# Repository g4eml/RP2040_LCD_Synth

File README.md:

# RP2040_LCD_Synth

## Description

This Project is a development of the RP2040_Synth project with the addition of a Touch screen LCD display module, refered to here as the HMI Module (Human Machine Interface). This is intended to be used as a piece of test equipment. 
Currently supports 4 different type of synthesiser chip, the ADF4351, the Max2870, the LMX2595 and the ADF5355.

## Features

Control and configuration can be done from the Touch Screen or from a USB serial port connection. 

No special programming hardware or software required. 

Serial programming using the RP2040s built in USB serial port and standard boot loader. 

Settings are saved to EEPROM for automatic load on power on.

Support for FSK CW Identification for beacon use.

Supports data modes for Beacon Identification.  JT4G is available on all chip types. Q65 is only available on the LMX2595 and ADF5355.

Note:- Whilst JT4G mode is available on all chips there may be some limitations. The ADF4351 and MAX2870 chips have a limited frequency resolution and may not be able to accurately set the required tone frequencies especially when an external multiplication chain is used.

Supports GPS connection for the accurate timing required for data modes. 

Supports 10 different channels which can also be selected by external switches. 

Supports External Key Input with independently configurable FSK Shift. 

Default register settings can be loaded for all synthesiser types to produce some initial RF output. This is often the hardest thing to do with a new chip type.

Supports use with an external frequency multiplier for the higher microwave bands. Allows frequency entry and display of the final output frequency. Adjusts FSK shifts to compensate for multiplication factor.  

Direct output frequency and phase detector frequency entry. Register values are calculated automatically.  

## Requirements

This code was designed to work with the Elecrow CrowPanel Pico-3.5 inch 480x320 TFT LCD HMI Module. https://www.aliexpress.com/item/1005007250778536.html 

Note:- similar HMI Panels are available using the ESP32 processor chip. Make sure that you are purchasing the RP2040 version. 

## Alternative Display

The correct module now appears to be difficult to obtain. A new interface board has been designed to allow a Raspberry Pi Pico to be fitted to a more easily available 3.5" TFT touch panel. Full Details can be found in the PCB folder. 

The LCD screen, controller chip and Touch Screen controller appear to be exactly the same as the original module.
 
If you are searching for these online the critical points are that it needs to be a 3.5" display  320 x 480 resolution with an ILI9488 controller and touch screen. 
There are lots of similar displays out there but the correct ones are usually Red and have 14 connections at one end of the board and 4 connections at the other. Be careful as these are also available without the touch screen. 
Full schematic and PCB designs are in the PCB folder. 

## Synthesisers

Suitable Synthesiser boards are available from Ebay, Amazon, Ali Express, SV1AFN etc. 

If you wish to use the data modes you will also need a GPS module to provide the necessary accurate timing.  

## Connecting

All of the various synthesiser moduels use different connectors and pinouts.

The simplest solution is to make an adaptor cable that plugs into the GP connector of the HMI module and fit suitable plugs for the modules to the other end. Keep the wiring as short as possible. Probably no more than 100mm long. 

The power can be provided by the USB-C connector marked 'USB' on the end of the HMI module

## Programming or updating the HMI Module (quick method)

This can be done either before or after the Syntesiser has been connected, it makes no difference. Updating to a new firmware version is done the same way.   

1. Locate the latest compiled firmware file 'RP2040_LCD_Synth.uf2' which will be found here https://github.com/g4eml/RP2040_LCD_Synth/releases and save it to your desktop. 

2. Connect the HMI Module to your PC using the USB-C port on the side. 

3. Hold down the BOOT button on the back of the HMI module and briefly press the Reset button. The RP2040 should appear as a USB disk drive on your PC.

3. Copy the .uf2 file onto the USB drive. The RP2040 will recognise the file and immediately update its firmware and reboot.

## Building your own version of the firmware (longer method and not normally required)

The RP2040 is programmed using the Arduino IDE with the Earl F. Philhower, III  RP2040 core. 

#### Installing the Arduino IDE

1. Download and Install the Arduino IDE 2.3.0 from here https://www.arduino.cc/en/software

2. Open the Arduino IDE and go to File/Preferences.

3. in the dialog enter the following URL in the 'Additional Boards Manager URLs' field: https://github.com/earlephilhower/arduino-pico/releases/download/global/package_rp2040_index.json

4. Hit OK to close the Dialog.

5. Go to Tools->Board->Board Manager in the IDE.

6. Type “RP2040” in the search box.

7. Locate the entry for 'Raspberry Pi Pico/RP2040 by Earle F. Philhower, III' and click 'Install'

### Installing the required libraries

1. From the Arduino IDE select (Tools > Manage Libraries)
2. Search for 'JTEncode' Scroll down to find the Etherkit JTEncode library by Jason Milldrum.
3. Click Install
4. Now search for 'TFT_eSPI' and find the TFT graphics library by Bodmer.
5. Click Install

#### Downloading the Software.

1. Download the latest released source code .zip file from https://github.com/g4eml/RP2040_LCD_Synth/releases

2. Save it to a convenient location and then unzip it.

The TFT_eSPI Library is unusual in that it needs to be configured to the TFT display in use by modifying library files. The required modified versions of the files are located in the 'LCD-eSPI Settings' folder of this repository. Copy the files 'Setup_Elecraft_HMI.h' and 'User_Setup_Select.h' from the downloaded 'LCD-eSPI Settings' folder to your Arduino libraries directory. This will normaly be found at 'Documents/Arduino/libraries/TFT_eSPI'

#### Programming the RP2040

1. Open the Arduino IDE and click File/Open

2. Navigate to the File RP2404Synth/RP2040_LCD_Synth.ino (downloaded in the previous step) and click Open.

3. Select Tools and make the following settings.

   Board: "Raspberry Pi Pico"
   
   Debug Level: "None"

   Debug Port: "Disabled"

   C++ Exceptions: "Disabled"

   Flash Size: "2Mb (no FS)"

   CPU Speed: "133MHz"

   IP/Bluetooth Stack: "IPV4 Only"

   Optimise: "Small (-Os)(standard)"

   RTTI: "Disabled"

   Stack Protection: "Disabled"

   Upload Method: "Default (UF2)"

   USB Stack: "Pico SDK"  

5. Connect the HMI Module to the USB port, hold down the BOOT button and briefly press the reset Button. 

6. Click Sketch/Upload.

The Sketch should compile and upload automatically to the Pico. If the upload fails you may need to disconnect the module and then hold down the BOOT button while reconnecting. 

## Connections

The pinout of the various Synthesiser modules tends to vary so it is difficult to give exact wiring diagrams.
The LMX2595 takes a lot of current so is best supplied from the USB 5V line using its own 3V3 regulator. The other chips can be powered from the 3V3 output of the HMI module. Power arrangements may need additional attention to minimise phase noise. 
The HMI module does not have a connector for the USB 5V supply. You may need to add your own additional wire for this. 

The generic wiring instructions are as follows:-

| HMI Module | ADF4351 | MAX2870 | LMX2595 | ADF5355 |
| :---:  |  :---:  |  :---:  |   :---: |  :---:  |
|5V      |   N/C   |   N/C   |    5V   |   5V   |
|3V3     |   3V3   |   3V3   |   N/C   |  N/C   |
|GND     |   GND   |   GND   |   GND   |  GND   |
|GPO3    |   CE    |   CE    |   CE    |   CE   |
|GPO4    |   MUX   |   MUX   |  MUXout |  MUX   |
|GPO5    |   LE    |   LE    |   CSB   |  LE    |
|GPO6    |   CLK   |   CLK   |   SCK   |  CLK  |
|GPO7    |   DAT   |   DATA  |   SDI   |  DAT  |

The firmware also supports the optional connection of a GPS module. This is used to accurately set the time, which is needed for the data modes. It is not needed for Local Oscillator or a CW only beacon. Any GPS module with a 3V3 output can be used. It needs to output NMEA data at 9600 Baud. One of the low cost NEO6M modules was used for development. 

| HMI Module | GPS Module |
| :---:  |    :---:   |
|GP0     |Rx          |
|GP1     |Tx          |

4 switches can be used to select the operating channel. (These are optional. If they are not used the power-up channel can be selected using the menu.)
The 4 inputs have internal pull up resistors to 3.3V. All that is needed is 4 switches to connect the pins to ground. 
Inverted logic is used. A grounded pin is read as a Logic 1. A floating pin is read as a logic 0.
For example, all pins left open circuit is read as channel 0. 

An external Morse Key can be connected between GP27 and Ground. This can be configured for FSK keying using the K Menu Option. 

| HMI Module | Function |
| :---:  |    :---:   |
|GP19    |Bit 0  Channel 1|
|GP20    |Bit 1  Channel 2|
|GP21    |Bit 2  Channel 4|
|GP26    |Bit 3  Channel 8|
|GP27    |External Key|

## Firmware description

On first use the screen will show the Touch calibration screen. Follow the instructions and touch each of the four corners of the screen. 

By default on power up the firmware will immediately send the EEPROM saved register values to the sunthesiser chip.  If the CW ident feature is enabled the ident will begin. If the Data mode is enabled the Data sequence will begin. Note that this will initially not be correctly timed. Once the GPS aquires its satellites the timing will synchronise. 

## Main Screen

The main screen allows entry of output frequency, power setting and output On/Off. 

To change a value just click on the black box and a pop-up alphabetic or numeric keypad will appear. 

10 separate channels (memories) can be selected. 

The power setting is the value sent to the Synthesiser chip, the available range of values will be chip dependent. See the relevant datasheets for more details. 

Entry to the configuration screen is by the Config button. 

The Save button will save the current settings to the selected Channel. 

## Configuring directly from the LCD Screen config page. 

Configuration should be straightforward. First select the Synthesiser type, then enter the Reference Oscillator Frequency and PFD.  CW Ident and /or JT Mode can be configured if required. 
When complete select Exit to return to the main screen. Then on the main screen select Save to save the new settings to EEPROM. 

## Using the USB serial port and a terminal program such as Putty or Terraterm. Pressing any key should result in the menu being displayed.

### Commands
Commands are entered by a single key press. Text and numbers require a carriage return to enter. Pressing Question Mark will usually give more detailed help. 
Changes to registers and parameters will be applied immediatey so you should be able to observe the result of the change in real time. 

#### The first three Menu Items are common to all channels. 

T = Select Chip Type. Allows the Synthesiser chip type to be selected. Normally only needed the first time you configure the firmware. This will also clear all memories and reset them to the default settings. 

O = Set Reference Oscillator Frequency. Sets the Reference Oscillator Frequency. Enter the actual frequency of your reference including any frequency error. The firmware will attempt to adjust for this. 

N = Set Channel Number. Enter the channel number from 0 to 9. This channel will then be loaded and you can adjust the settings using the menu. This overrides the channel selected by any external switches. if you wish to use external switches to select a channel then you must change this setting to 255 before saving the EEPROM. A setting of 255 enables external channel selection. 

#### The following menu settings are applied to the currently selected channel. Each channel may have different settings. 

D = Restores the Default Register Values for chip. Sets default values to all registers. Tries to program a 10Mhz PFD and requests a frequency. After this your Synthesiser should start to output RF. 

P = Enter PFD Frequency. Set the required PFD frequency. The firmware will attempt to get as close as possible to the requested value but not all values can be achieved.

M = Set External Multiplier. If the Synthesiser is followed by a multiplier for higher frequencies this option allows you to specify the multiplcation factor. Final Multiplied Frequencies can then be entered and viewed. 

F = Enter Output Frequency. Set the required output frequency. The firmware will attempt to calculate the closest register values to achieve this. Changing the PFD may improve the result. 

C = Calculate and display frequency from current settings. The firmware will calculte the expected output frequency from the current register settings. Useful to check after youy make manual changes.

V = View / Enter Variables for Registers. Allows viewing or entry of parameters using the same names as defined in the chip datasheet. Press ? for a full list of the available parameter names. 

R = View / Enter Registers Directly in Hex. Allws direct entry of regiser values in Hexadecimal. Useful when transfering values calculated by another program. 

I = Configure CW Ident. Alows entry of CW Ident, CW Speed, Ident Period and FSK Shift.  A shift of -800Hz is a typical value. Ident period is only valid for a CW only configuration. If a JT mode is also enbled then the CW ident will be sent every odd minute. 

J = Configure data modes. Allows entry of a 13 character message for JT4G. This would normally be the Callsign and Maidenhead locator. For Q65 this must be the callsign and 4 character locator. The ident will be sent every Even minute. Accurate timing requires a GPS module to be connected.

K = Configure External Key. An External Morse key can be connected and used to frequency shift the signal. The FSK Shift can be entered and is seperate from the CWID shift. 

G = View GPS NMEA data. This is used to test the GPS connection. when selected it will echo all GPS data to the screen. Press any key to exit this mode. 

S = Save Registers to EEPROM. Saves the current Synthesiser settings to EEPROM. They will then be automatically loaded on the next power cycle. You must do this at least once. 

X = Exit Menu. Exits from the menu, re-initialises the Synthesiser and starts the CW Ident. 

##

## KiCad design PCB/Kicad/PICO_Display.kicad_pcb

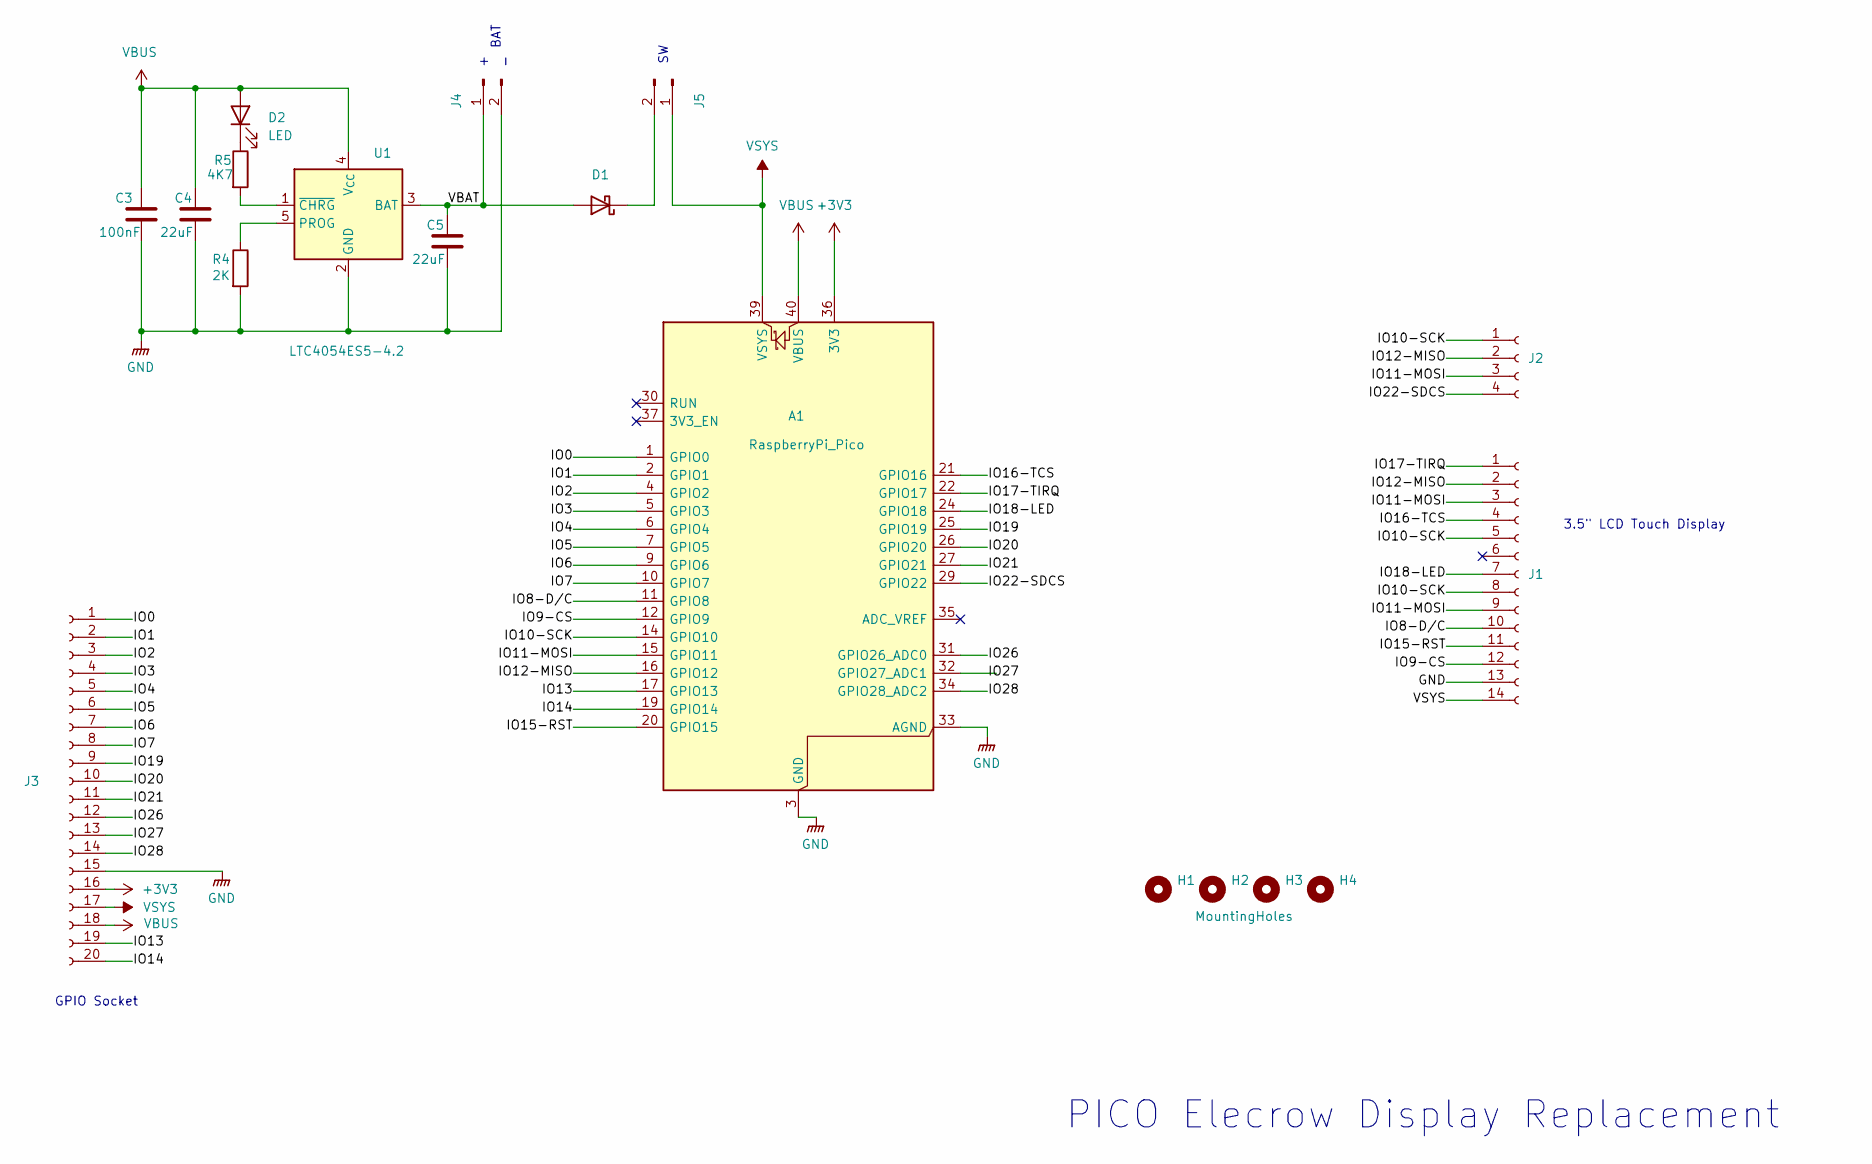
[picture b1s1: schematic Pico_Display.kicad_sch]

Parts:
A1: RaspberryPi_Pico; RaspberryPi_Pico_Common_THT
C3: 100nF; C_0805_2012Metric_Pad1.18x1.45mm_HandSolder
C4, C5: 22uF; C_0805_2012Metric_Pad1.18x1.45mm_HandSolder
D1: D_Schottky; D_SOD-123F
D2: LED; LED_0805_2012Metric_Pad1.15x1.40mm_HandSolder
H1, H2, H3: MountingHole; MountingHole_3.2mm_M3_ISO14580_Pad
H4: MountingHoles; MountingHole_3.2mm_M3_ISO14580_Pad
J1: Conn_01x14_Socket; PinSocket_1x14_P2.54mm_Vertical
J2: Conn_01x04_Socket; PinSocket_1x04_P2.54mm_Vertical
J3: Conn_01x18_Socket; PinSocket_1x20_P2.54mm_Vertical
J4, J5: Conn_01x02_Pin; JST_XH_B2B-XH-A_1x02_P2.50mm_Vertical
R4: 2K; C_0805_2012Metric_Pad1.18x1.45mm_HandSolder
R5: 4K7; C_0805_2012Metric_Pad1.18x1.45mm_HandSolder
U1: LTC4054ES5-4.2; TSOT-23-5

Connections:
+3V3: A1.36 (3V3), J3.16
/IO0: A1.1 (GPIO0), J3.1
/IO1: A1.2 (GPIO1), J3.2
/IO2: A1.4 (GPIO2), J3.3
/IO3: A1.5 (GPIO3), J3.4
/IO4: A1.6 (GPIO4), J3.5
/IO5: A1.7 (GPIO5), J3.6
/IO6: A1.9 (GPIO6), J3.7
/IO7: A1.10 (GPIO7), J3.8
/IO8-D/C: A1.11 (GPIO8), J1.10
/IO9-CS: A1.12 (GPIO9), J1.12
/IO10-SCK: A1.14 (GPIO10), J1.5, J1.8, J2.1
/IO11-MOSI: A1.15 (GPIO11), J1.3, J1.9, J2.3
/IO12-MISO: A1.16 (GPIO12), J1.2, J2.2
/IO13: A1.17 (GPIO13), J3.19
/IO14: A1.19 (GPIO14), J3.20
/IO15-RST: A1.20 (GPIO15), J1.11
/IO16-TCS: A1.21 (GPIO16), J1.4
/IO17-TIRQ: A1.22 (GPIO17), J1.1
/IO18-LED: A1.24 (GPIO18), J1.7
/IO19: A1.25 (GPIO19), J3.9
/IO20: A1.26 (GPIO20), J3.10
/IO21: A1.27 (GPIO21), J3.11
/IO22-SDCS: A1.29 (GPIO22), J2.4
/IO26: A1.31 (GPIO26_ADC0), J3.12
/IO27: A1.32 (GPIO27_ADC1), J3.13
/IO28: A1.34 (GPIO28_ADC2), J3.14
/VBAT: C5.2, D1.2 (A), J4.1, U1.3 (BAT)
GND: A1.3 (GND), A1.8 (GND), A1.13 (GND), A1.18 (GND), A1.23 (GND), A1.28 (GND), A1.33 (AGND), A1.38 (GND), C3.1, C4.1, C5.1, J1.13, J3.15, J4.2, R4.2, U1.2 (GND)
unnamed: D1.1 (K), J5.2
unnamed: D2.1 (K), R5.1
unnamed: R4.1, U1.5 (PROG)
unnamed: R5.2, U1.1 (~CHRG)
VBUS: A1.40 (VBUS), C3.2, C4.2, D2.2 (A), J3.18, U1.4 (V_{CC})
VSYS: A1.39 (VSYS), J1.14, J3.17, J5.1

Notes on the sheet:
PICO Elecrow Display Replacement
BAT
3.5" LCD Touch Display
GPIO Socket

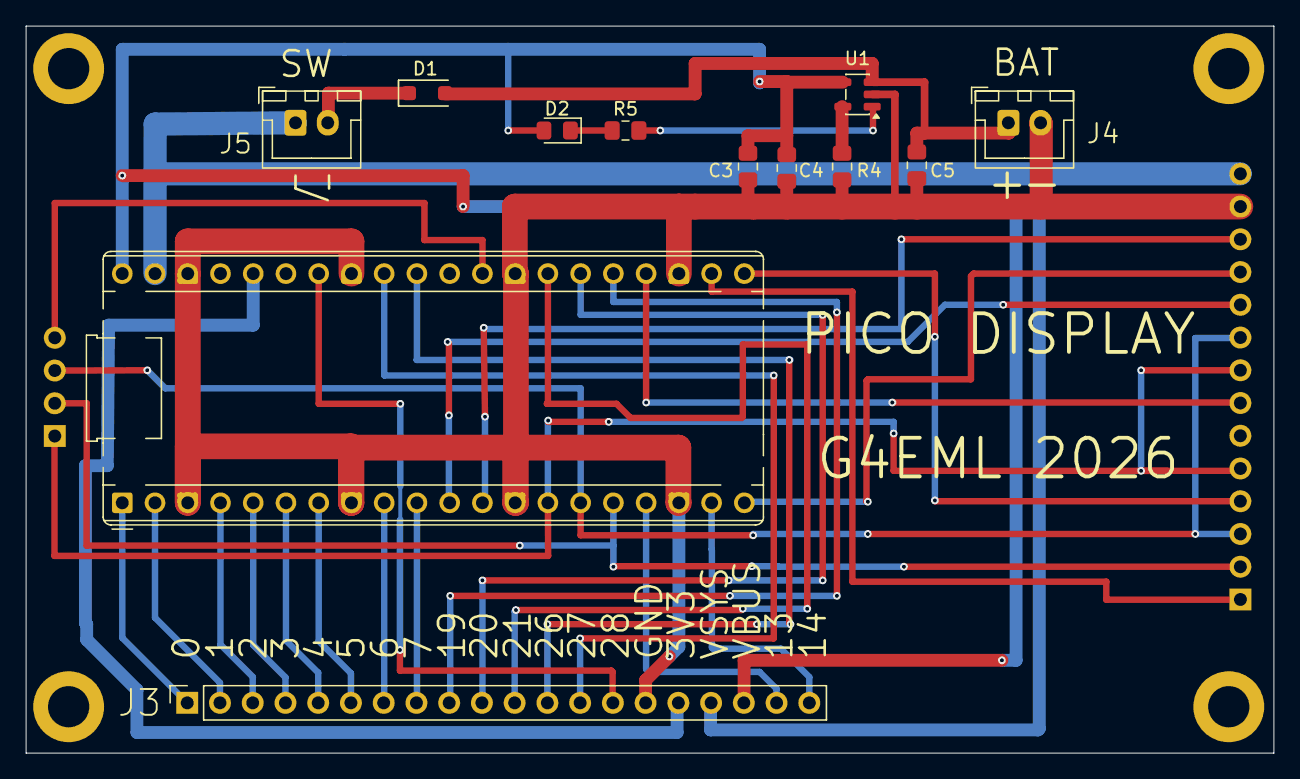
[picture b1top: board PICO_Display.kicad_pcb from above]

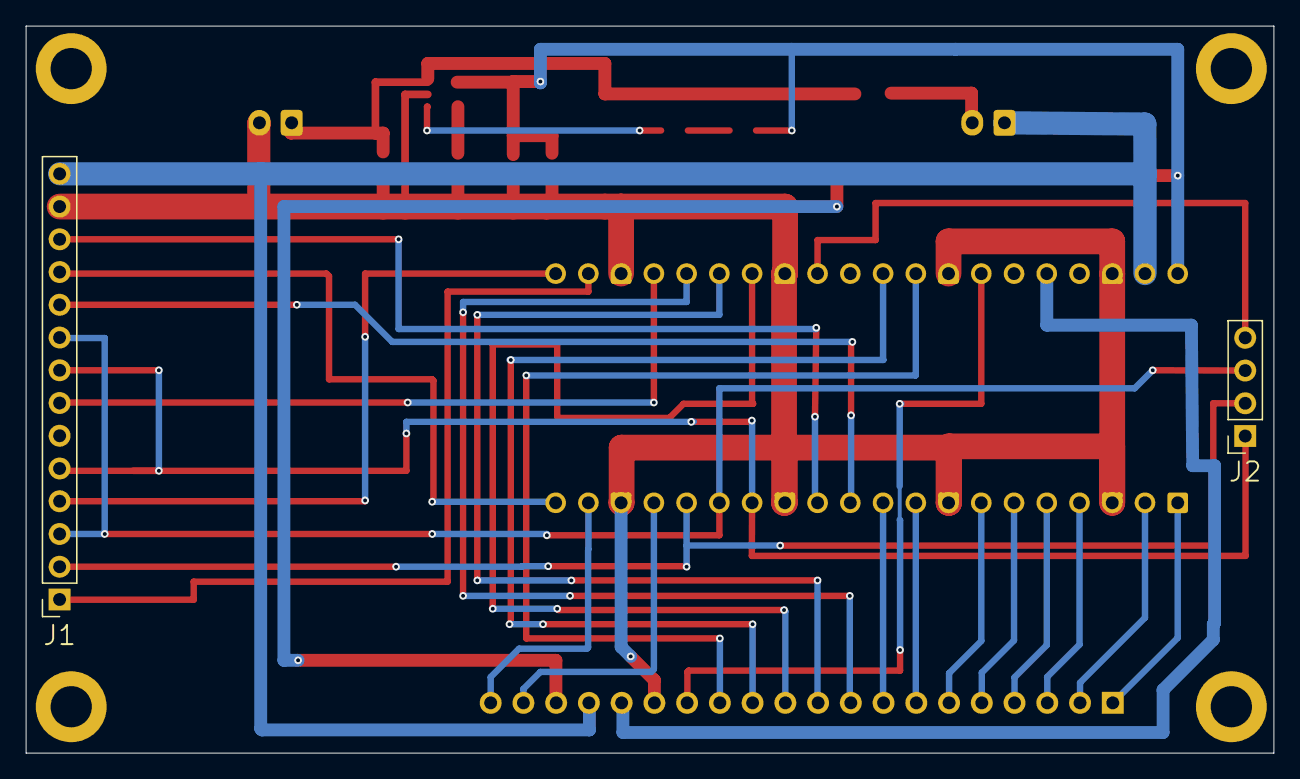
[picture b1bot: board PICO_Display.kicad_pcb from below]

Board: 2 copper layers, 96.8 x 56.4 mm, 18 parts (2 on the bottom side), 35 nets.

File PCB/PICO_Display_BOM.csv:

"Id";"Designator";"Footprint";"Quantity";"Designation";"Supplier and ref";
1;"A1";"RaspberryPi_Pico_Common_THT";1;"RaspberryPi_Pico";;;
2;"C3";"C_0805_2012Metric_Pad1.18x1.45mm_HandSolder";1;"100nF";;;
3;"C4, C5";"C_0805_2012Metric_Pad1.18x1.45mm_HandSolder";2;"22uF";;;
4;"D1";"D_SOD-123F";1;"D_Schottky";;;
5;"D2";"LED_0805_2012Metric_Pad1.15x1.40mm_HandSolder";1;"LED";;;
6;"J1";"PinSocket_1x14_P2.54mm_Vertical";1;"Conn_01x14_Socket";;;
7;"J2";"PinSocket_1x04_P2.54mm_Vertical";1;"Conn_01x04_Socket";;;
8;"J3";"PinSocket_1x20_P2.54mm_Vertical";1;"Conn_01x18_Socket";;;
9;"J4, J5";"JST_XH_B2B-XH-A_1x02_P2.50mm_Vertical";2;"Conn_01x02_Pin";;;
10;"R4";"C_0805_2012Metric_Pad1.18x1.45mm_HandSolder";1;"2K";;;
11;"R5";"C_0805_2012Metric_Pad1.18x1.45mm_HandSolder";1;"4K7";;;
12;"U1";"TSOT-23-5";1;"LTC4054ES5-4.2";;;

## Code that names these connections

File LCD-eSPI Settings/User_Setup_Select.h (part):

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
// These are the pins for ESP8266 boards
//      Name   GPIO    NodeMCU      Function
#define PIN_D0  16  // GPIO16       WAKE
#define PIN_D1   5  // GPIO5        User purpose
#define PIN_D2   4  // GPIO4        User purpose
#define PIN_D3   0  // GPIO0        Low on boot means enter FLASH mode
#define PIN_D4   2  // GPIO2        TXD1 (must be high on boot to go to UART0 FLASH mode)
#define PIN_D5  14  // GPIO14       HSCLK
#define PIN_D6  12  // GPIO12       HMISO
#define PIN_D7  13  // GPIO13       HMOSI  RXD2
#define PIN_D8  15  // GPIO15       HCS    TXD0 (must be low on boot to enter UART0 FLASH mode)
#define PIN_D9   3  //              RXD0
#define PIN_D10  1  //              TXD0

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
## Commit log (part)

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2024-11-19 Fix Jt4 Bug
2024-11-25 Add JT Tone 1 Offset and warnings
2024-11-25 Update JT Modes
2025-03-15 Add MHz Text
2025-03-15 Force memory clear on chip change
2025-03-18 Add Memory Select page
2025-03-18 add rounded boxes
2025-03-18 Improve save button
2025-03-19 Improve GPS Handling
2025-03-19 Add CW Enable Button
2025-03-24 Change GPS Time Message
2025-04-20 Fix ADF4351 Bug
2025-04-21 Increase Oscillator allowable Frequencies
2025-04-21 Add Touchscreen recalibration
    Force touchscreen recalibration if the screen is touched during power on.
2025-09-06 Fix CW Shift
2025-09-06 Fi FSK Shifts
2025-09-09 add bat display
2025-09-10 Add Battery Display
2025-09-10 Battery Auto Detect
2025-09-17 Update LCD files
2025-12-16 Q65 Update
2025-12-16 Revise README for RP2040_LCD_Synth project
    Updated project description and features in README.
2025-12-30 add adf5355
2026-01-04 Add ADF5355 support and update project details
    Updated README to include ADF5355 support and minor corrections.
2026-01-04 Add Unlock Display
